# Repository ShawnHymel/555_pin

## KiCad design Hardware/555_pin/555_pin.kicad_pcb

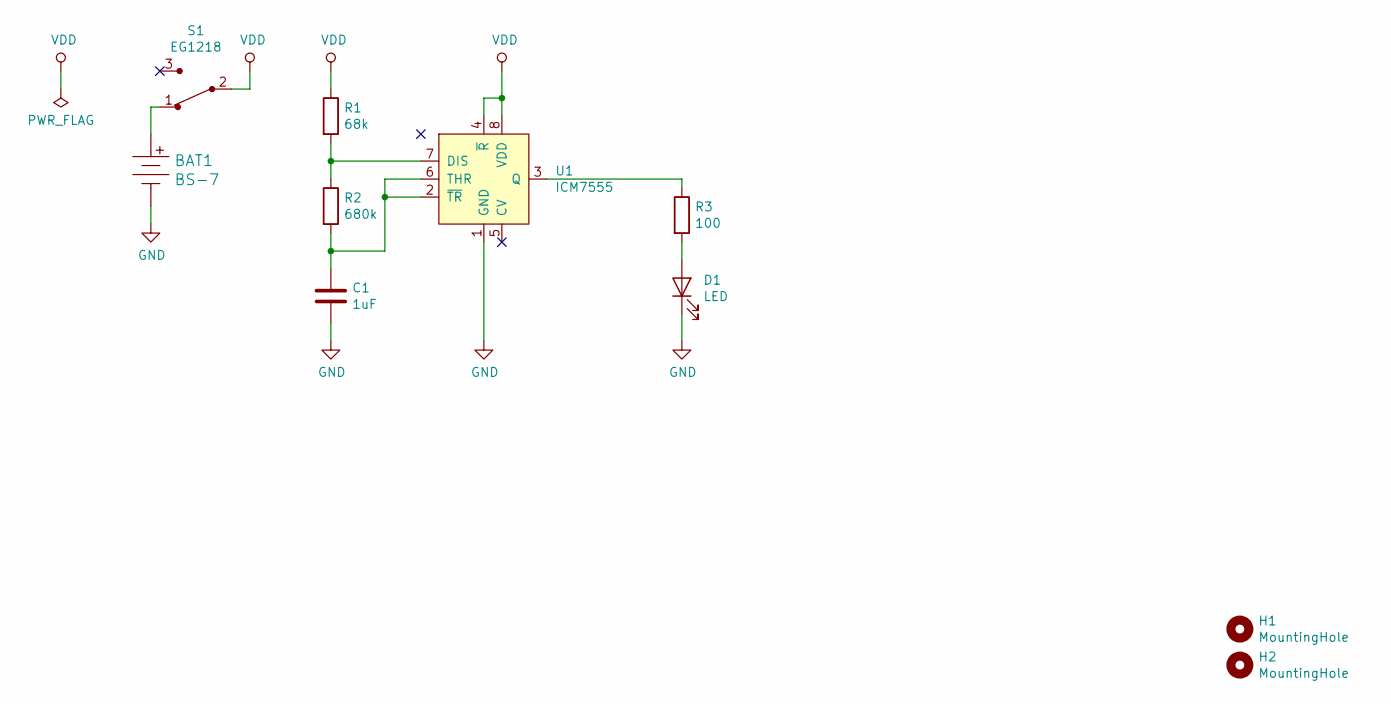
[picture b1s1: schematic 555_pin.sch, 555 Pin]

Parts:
BAT1: BS-7; Battery_Holder_Coin_2032_BS-7; MPN BS-7; Digi-Key_PN BS-7-ND
C1: 1uF; C_Disc_D3.0mm_W1.6mm_P2.50mm
D1: LED; LED_D5.0mm
H1, H2: MountingHole; MountingHole_3.2mm_M3
R1: 68k; R_Axial_DIN0207_L6.3mm_D2.5mm_P7.62mm_Horizontal
R2: 680k; R_Axial_DIN0207_L6.3mm_D2.5mm_P7.62mm_Horizontal
R3: 100; R_Axial_DIN0207_L6.3mm_D2.5mm_P7.62mm_Horizontal
S1: EG1218; Switch_Slide_11.6x4mm_EG1218; MPN EG1218; Digi-Key_PN EG1903-ND
U1: ICM7555; ICM7555_DIP

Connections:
GND: BAT1.Neg, C1.2, D1.1 (K), U1.1 (GND)
unnamed: BAT1.Pos, S1.1
unnamed: C1.1, R2.2, U1.2 (~TR), U1.6 (THR)
unnamed: D1.2 (A), R3.2
unnamed: R1.2, R2.1, U1.7 (DIS)
unnamed: R3.1, U1.3 (Q)
VDD: R1.1, S1.2, U1.4 (~R), U1.8 (VDD)

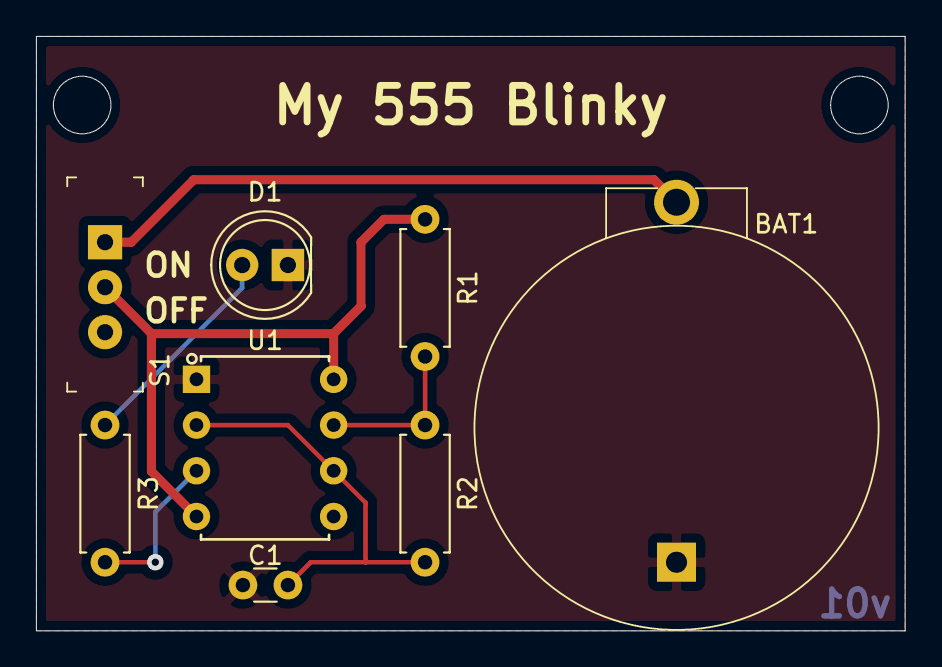
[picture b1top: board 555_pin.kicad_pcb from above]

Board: 2 copper layers, 48.3 x 33.0 mm, 10 parts (0 on the bottom side), 7 nets.

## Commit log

2019-12-01 Schematic and layout done

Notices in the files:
Hardware/555_pin/555_pin.sch:
creativecommons.org/licenses/by/4.0
License: CC BY 4.0
